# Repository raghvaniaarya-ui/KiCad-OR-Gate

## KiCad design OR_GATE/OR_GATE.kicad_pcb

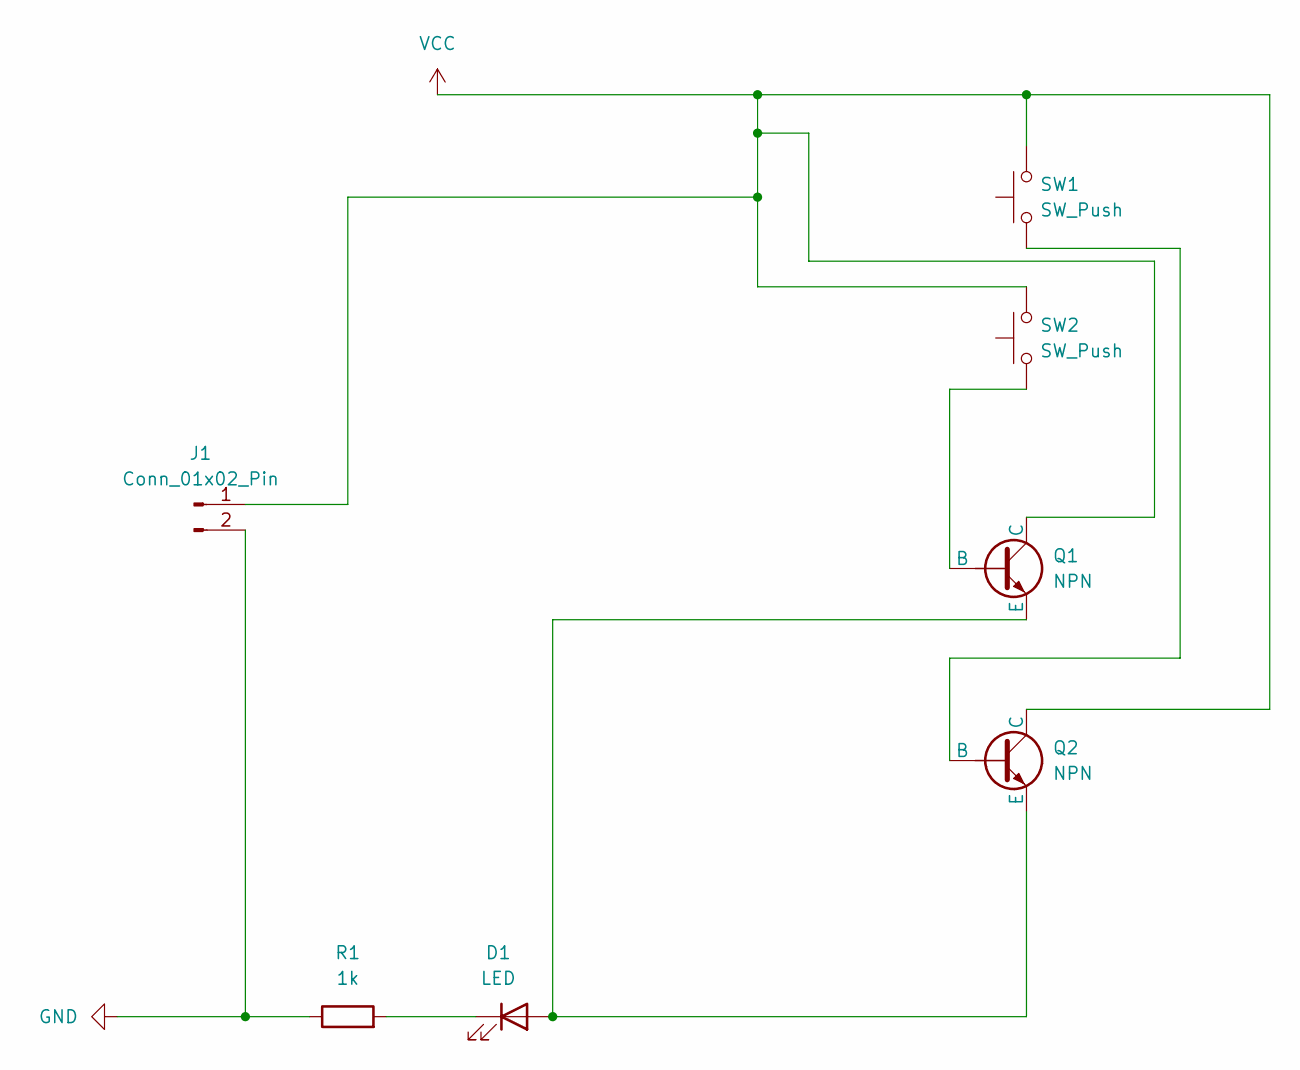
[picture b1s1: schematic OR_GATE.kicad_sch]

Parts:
D1: LED; LED_D5.0mm
J1: Conn_01x02_Pin; PinHeader_1x02_P2.54mm_Vertical
Q1, Q2: NPN; TO-92_Inline
R1: 1k; R_Axial_DIN0207_L6.3mm_D2.5mm_P7.62mm_Horizontal
SW1, SW2: SW_Push; SW_PUSH-12mm_Wuerth-430476085716

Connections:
GND: J1.2, R1.1
unnamed: D1.2 (A), Q1.3 (E), Q2.3 (E)
unnamed: D1.1 (K), R1.2
unnamed: Q1.2 (B), SW2.1
unnamed: Q2.2 (B), SW1.1
VCC: J1.1, Q1.1 (C), Q2.1 (C), SW1.2, SW2.2

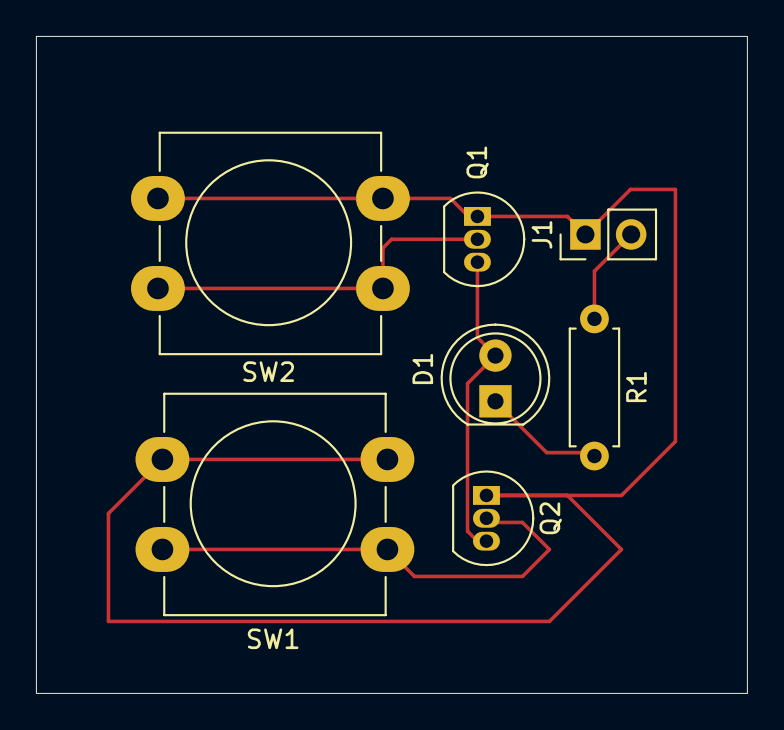
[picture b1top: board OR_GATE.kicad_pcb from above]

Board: 2 copper layers, 39.5 x 36.5 mm, 7 parts (0 on the bottom side), 6 nets.
